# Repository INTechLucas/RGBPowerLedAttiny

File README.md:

# RGBPowerLedAttiny
Tiny board controlling a high power RGB LED with an ATtiny85

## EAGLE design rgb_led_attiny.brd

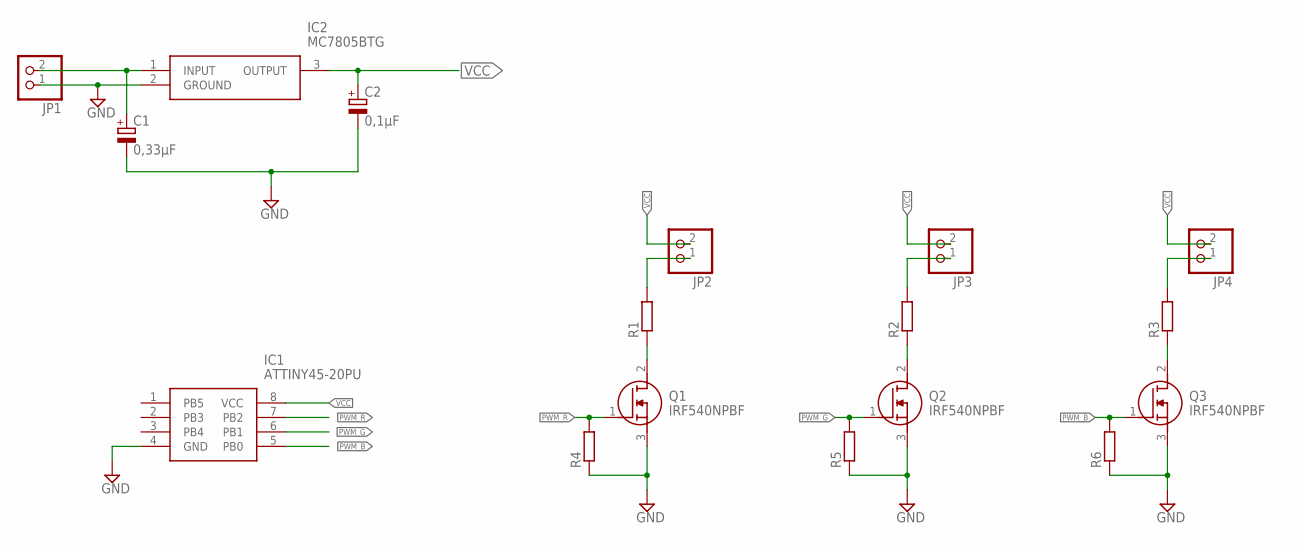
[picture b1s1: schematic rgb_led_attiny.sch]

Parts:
C1: 0,33µF; E2,5-6
C2: 0,1µF; E2,5-6
IC1: ATTINY45-20PU; DIP254P762X533-8
IC2: MC7805BTG; TO254P482X997X2018-3P
JP1, JP2, JP3, JP4: PINHD-1X2; 1X02
Q1, Q2, Q3: IRF540NPBF; TO254P469X1042X1967-3P
R1, R2, R3: R-EU_0613/5V; P0613V
R4, R5, R6: R-EU_0207/10; 0207/10

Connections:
GND: C1.-, C2.-, IC1.4 (GND), IC2.2 (GROUND), JP1.1, Q1.3 (S), Q2.3 (S), Q3.3 (S), R4.1, R5.1, R6.1
unnamed: C1.+, IC2.1 (INPUT), JP1.2
unnamed: Q2.2 (D), R2.1
unnamed: Q1.2 (D), R1.1
unnamed: JP2.1, R1.2
unnamed: JP3.1, R2.2
unnamed: Q3.2 (D), R3.1
unnamed: JP4.1, R3.2
PWM_B: IC1.5 (PB0), Q3.1 (G), R6.2
PWM_G: IC1.6 (PB1), Q2.1 (G), R5.2
PWM_R: IC1.7 (PB2), Q1.1 (G), R4.2
VCC: C2.+, IC1.8 (VCC), IC2.3 (OUTPUT), JP2.2, JP3.2, JP4.2

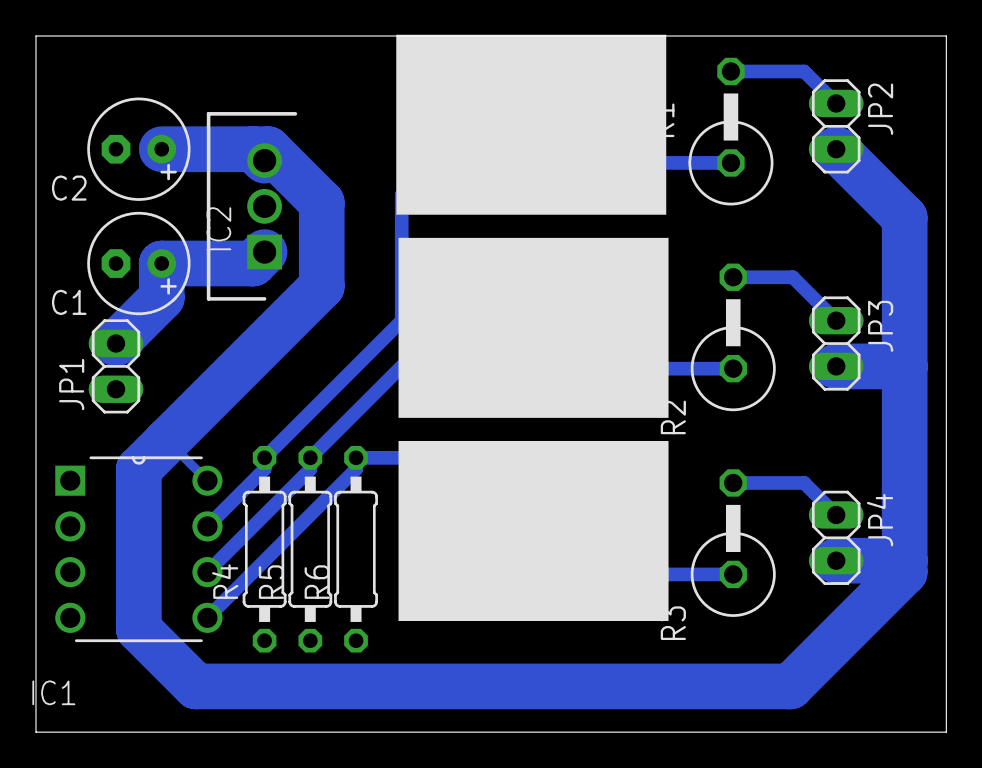
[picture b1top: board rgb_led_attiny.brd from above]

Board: 2 copper layers, 50.6 x 38.7 mm, 17 parts (0 on the bottom side), 12 nets.

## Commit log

2019-03-19 Début d'ajout des composants, cablage du régulateur
2019-03-19 Premier jet du schematic
2019-03-19 Premier placement des composants
2019-03-19 Premier routage
2019-03-22 Deuxième routage, plus compact avecles resistances en vertical. Ajout de pull-down sur le gate des MOSFETs
2019-03-22 Encore un peu de gain de place
